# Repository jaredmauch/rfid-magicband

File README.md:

# rfid-magicband

This repo includes the PCB layout for a ItsyBitsy M4 to Raspberry Pi Zero setup to adapt with a MFRC522 board and NeoPixel ring and Adafruit LiIon/LiPoly Backpack to provide for mobile reading of RFID devices, including things like the Magic Bands and park tickets.

You can configure on the Raspberry Pi a whitelist of the cards that are permissible to make the ring go green.

This is mostly an example and reference for others and I may update it as I refine the hardware and software over time.

Requirements:
Neopixel Ring
MFRC522
Raspberry Pi (zero - but pin compatible with any 40 pin Pi2-4)
ItsyBitsy M4 (M0 will also work)
PCB Adapter (from hardware directory, or breadboard it yourself)

Optional:
LiIon Battery/Backpack

It's recommended if you're in a theme park to turn off bluetooth, wifi, hdmi and anything else on the device that may cause power draw.  I may script something later that does this and makes installation easier.

I coded it in python3 and circuitpython because I'm not a heathen.

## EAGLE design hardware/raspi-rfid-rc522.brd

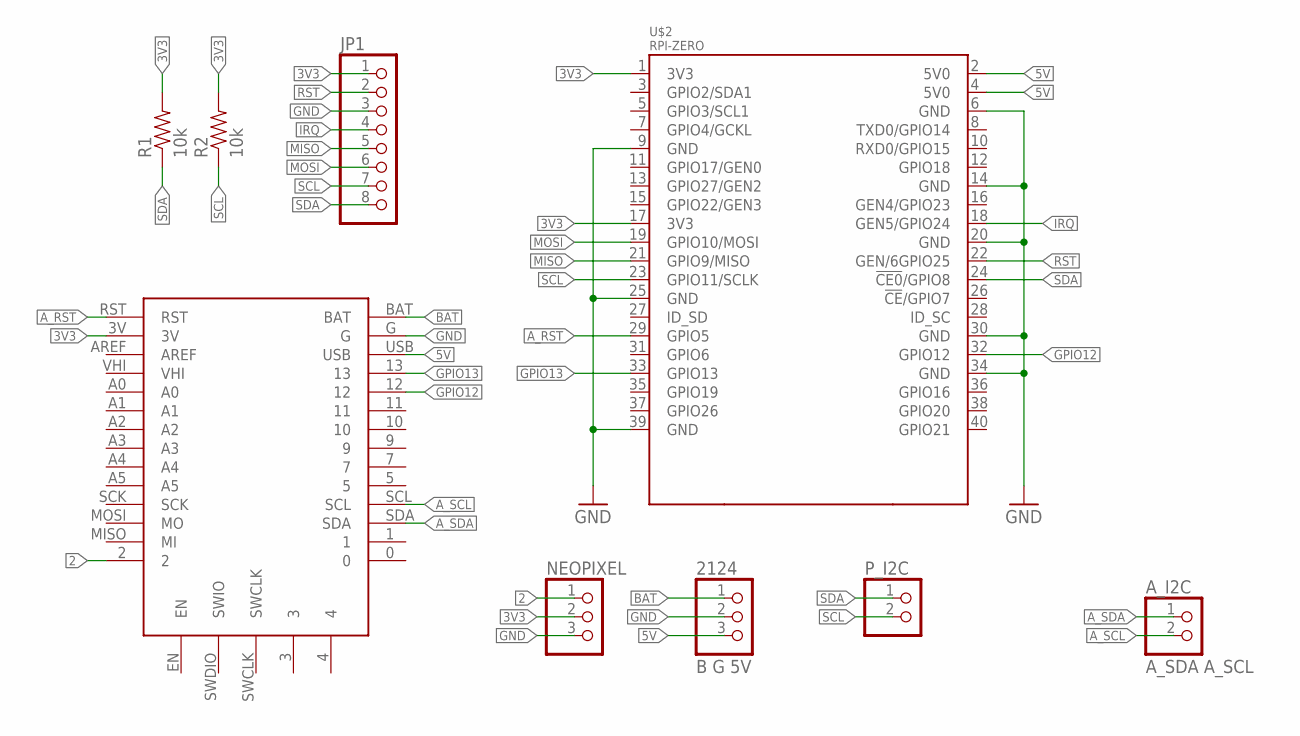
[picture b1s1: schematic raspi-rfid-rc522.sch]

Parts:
2124: B G 5V; 1X03
A_I2C: A_SDA A_SCL; 1X02
JP1: PINHD-1X8/90; 1X08/90
NEOPIXEL: PINHD-1X3; 1X03
P_I2C: PINHD-1X2; 1X02
R1, R2: 10k; 0603-RES
U$1: ITSYBITSYM4
U$2: RPI-ZERO; RASPBERRYPI_BASTELSTUBE_V13_RASPI_BOARD_B+_FULL

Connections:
2: NEOPIXEL.1, U$1.2
3V3: JP1.1, NEOPIXEL.2, R1.2, R2.2, U$1.3V, U$2.1 (3V3), U$2.17 (3V3)
5V: 2124.3, U$1.USB, U$2.2 (5V0), U$2.4 (5V0)
A_RST: U$1.RST, U$2.29 (GPIO5)
A_SCL: A_I2C.2, U$1.SCL
A_SDA: A_I2C.1, U$1.SDA
BAT: 2124.1, U$1.BAT
GND: 2124.2, JP1.3, NEOPIXEL.3, U$1.G, U$2.6 (GND), U$2.9 (GND), U$2.14 (GND), U$2.20 (GND), U$2.25 (GND), U$2.30 (GND), U$2.34 (GND), U$2.39 (GND)
GPIO12: U$1.12, U$2.32 (GPIO12)
GPIO13: U$1.13, U$2.33 (GPIO13)
IRQ: JP1.4, U$2.18 (GEN5/GPIO24)
MISO: JP1.5, U$2.21 (GPIO9/MISO)
MOSI: JP1.6, U$2.19 (GPIO10/MOSI)
RST: JP1.2, U$2.22 (GEN/6GPIO25)
SCL: JP1.7, P_I2C.2, R2.1, U$2.23 (GPIO11/SCLK)
SDA: JP1.8, P_I2C.1, R1.1, U$2.24 (!CE0!/GPIO8)

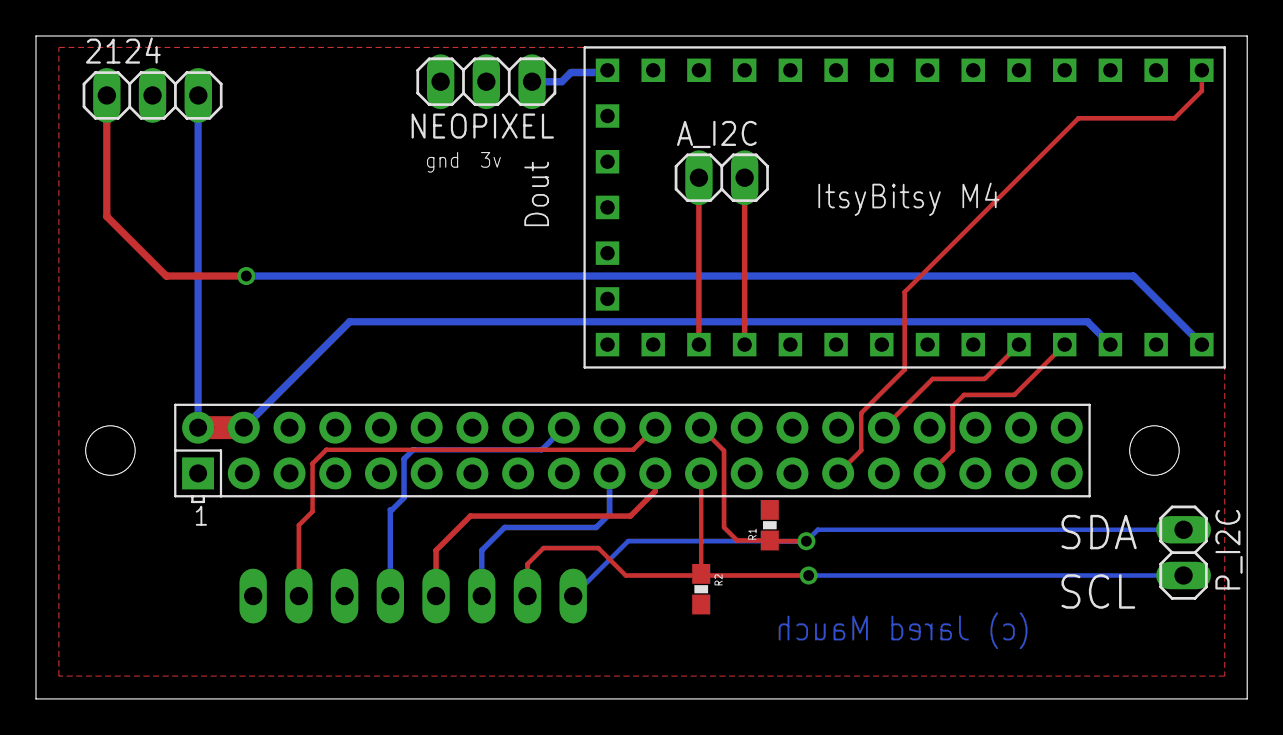
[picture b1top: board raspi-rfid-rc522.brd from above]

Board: 2 copper layers, 67.3 x 36.8 mm, 9 parts (1 on the bottom side), 16 nets.

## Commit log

2020-01-01 sync initial code up
2020-01-01 sync hardware
2020-01-03 add blue pulse
2020-01-08 turn off m4 led
2020-01-08 update pcb
